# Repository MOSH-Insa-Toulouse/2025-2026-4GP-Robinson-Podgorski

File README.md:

##### 2025-2026 Podgorski Romain et Robinson Yanis
# **Projet de Capteur Graphite**

## Table des matières
- [Projet de Gapteur Graphite](#projet-de-capteur-graphite)
- [Contexte](#contexte)
- [Réalisation du projet](#réalisation-du-projet)
  - [1. Conception du capteur graphite](#1-conception-du-capteur-graphite)
    - [1.1 Matériel utilisé pour ce projet](#11-matériel-utilisé-pour-ce-projet)
    - [1.2 Principe de fonctionnement du capteur graphite](#12-principe-de-fonctionnement-du-capteur-graphite)
  - [2. Simulation electronique du circuit amplificateur avec LTSpice](#2-simulation-electronique-du-circuit-amplificateur-avec-ltspice)
    - [2.1 Principe de fonctionnement](#21-principe-de-fonctionnement)
    - [2.2 Simulations](#22-simulations)
  - [3. Conception de la PCB avec KiCad](#3-conception-de-la-pcb-avec-kicad)
    - [3.1 Réalisation des empreintes et de la schématique](#31-réalisation-des-empreintes-et-de-la-schématique)
    - [3.2 Placement et routage](#32-placement-et-routage)
    - [3.3 Visualisation 3D et vérifications](#33-visualisation-3d-et-vérifications)
  - [4. Réalisation du shield](#4-réalisation-du-shield)
    - [4.1 Impression de la PCB](#41-impression-de-la-pcb)
    - [4.2 Montage et soudure](#42-montage-et-soudure)
  - [5. Ecriture du code Arduino](#5-ecriture-du-code-arduino)
  - [6. Développement de l'application android couplée au code arduino avec MIT App Inventor](#6-développement-de-lapplication-android-couplée-au-code-arduino-avec-mit-app-inventor)
  - [7. Banc de test](#7-banc-de-test)
  - [8. Datasheet](#8-Datasheet)
- [Conclusion](#conclusion)
- [Références](#références)
- [Contacts](#contacts)
  - [Étudiants](#étudiants)
  - [Enseignants](#enseignants)

---

# Contexte

Dans un monde où la complexification de conception, de fabrication, d'utilisation et de réparation des dispositifs electroniques et appareils entraînent certaines dérives environnementales et de surconsommation, le développement de la low-tech est enjeu majeur de ces prochaines années.  

Dans ce contexte et dans le cadre de notre formation au Génie Physique de l'INSA Toulouse, nous avons développé au cours de ce projet un capteur de flexion simple de conception, de réalisation et de réparation, basé sur du graphite de crayon à papier. Nous l'avons intégré au sein d'un circuit électronique interactif couplé à un microcontrôleur Arduino, pilotable grâce à un code arduino et une application Android.

Le but final de ce capteur est de pouvoir le comparer avec un capteur de flexion industriel, et pouvoir répondre à la question :
*Ce capteur peut-il remplacer un capteur flex industriel ?*

Ce projet a été effectué en différentes étapes documentées dans ce README.

# Livrables

Ce projet contient 4 différents livrables :  
* Un shield Arduino pour le circuit électronique de nos composants
* Un code Arduino qui gère les différents composants ainsi que le banc de test
* Une application android APK qui gère l'interface avec le Arduino
* Une dtasheet du capteur de flexion

---

# Réalisation du projet

## 1. Conception du capteur graphite

### 1.1 Matériel utilisé pour ce projet
Pour réaliser ce projet, nous avons utilisé les composants électroniques suivant :
* 1 capteur en graphite fabriqué avec la mine d'un crayon à papier
* 1 carte Arduino UNO Rev 3
* 1 module Bluetooth HC-05
* 1 écran OLED SSD 1306
* 1 encodeur rotatif Keyes KY-040
* 1 capteur de flexion commercial LLC 1070
* 1 potentiomètre numérique MCP41100
* 2 supports IC pour le potentiomètre et l'amplificateur

Pour la réalisation du circuit amplificateur transimpédance, nous avons utilisé :
* 1 amplificateur opérationnel LTC1050
* 2 résistance 1kΩ
* 1 résistance 10kΩ
* 2 résistances 100kΩ
* 2 condensateurs 100nF
* 1 condensateur 1µF

### 1.2 Principe de fonctionnement du capteur graphite

Les mines de crayon sont composées de fines particules de graphite liées entre elles par des liants argileux. Le capteur de flexion en graphite repose sur le dépôt de ces particules sur un papier. En effet, les traces de crayon peuvent être considérées comme des films minces conducteurs constitués d'un réseau granulaire désordonné de particules de graphite percolées sur le papier. Les mines de crayon plus dures contiennent une proportion plus élevée de liants argileux tandis que les mines plus tendres contiennent une proportion plus élevée de particules de graphite résultant à une résistance moins élevée.

Face à une déformation mécanique, le réseau de ces particules est affecté, et la conduction électrique, qui s'effectue par le biais des contacts entre les particules voisines(effet tunnel), est donc fortement modifiée, augmentant ou diminuant la résistance du capteur :
* Sous contraction, la distance entre les particules diminue, favorisant les contacts entre paritucles et diminuant la résistance.
* Sous extension, la distance entre les particules augmente, rendant les contacts entre particules compliqués et augmentant donc la résistance.

C'est ainsi que nous pouvons mesurer la variation de flexion grâce à la variation de résistance au sein du capteur.

---

## 2. Simulation electronique du circuit amplificateur avec LTSpice

### 2.1 Principe de fonctionnement

La première étape de ce projet consiste à simuler le circuit amplificateur grâce au logiciel LTSpice.

Le capteur en graphite possède une résistance variable de l'ordre du GΩ. Si l'on applique la tension de 5V fournie par notre carte Arduino, le courant généré sera très faible, de l'ordre de la dizaine de nA. IL est donc nécessaire d'utiliser un circuit amplificateur pour pouvoir traiter ce signal.

Pour cela, nous utilisons un montage amplificateur transimpédance, qui permet de convertir le courant faible reçu par le capteur en une tension suffisante pour le convertisseur analogique-numérique (ADC) d'une carte Arduino. Le schéma du montage transimpédance est comme suit :

La résistance de shunt R1 permet la conversion de courant à tension, afin d'accepter un courant entrant venant du capteur. Ce montage est amplificateur à fort gain, non-inverseur et a l'avantage de pouvoir fonctionner avec seulement une alimentation positive. Cependant, la chute de tension sur R1 perturbe un peu la tension appliquée au capteur.

Des contraintes sont néanmoins présente pour le choix de l'amplificateur opérationnel. En effet, il doit accepter un faible courant d'entrée et une ultra-faible offset de tension afin de ne pas fausser les valeurs de tension transmises à l'ADC. L'amplificateur LTC1050 répond à ces critères.

Pour compléter ce montage, il est nécessaire de rajouter des filtres. En effet, le montage est très sensible, et vulnérable au bruit 50 Hz, aux horloges de circuits digitaux (microcontrôleur, afficheur, etc...) et aux transceivers RF (bluetooth, etc...). Une bande passante de 1 Hz est largement suffisante pour extraire toute l'information utile du capteur. Un filtrage anti-repliement est aussi indispensable en raison de l'échantillonage effectué par l'ADC, et pour cela il est donc nécessaire de faire fonctionner l'ADC à la plus grande fréquence sans perte de qualité, qui est de 15.4 kHz pour pour l'Arduino UNO. Le montage final est donc comme suivant :

Dans ce montage, plusieurs filtres sont en action :
* un filtre passif avec R1 et C1, avec $f_{c}= 16$ Hz, pour éviter que les bruits en courant de haute fréquence ne causent de la distorsion dans l'étage d'entrée
* un filtre actif avec R3 et C4, avec $f_{c}= 1,6$ Hz,pour un maximum d'efficacité sur l'amplificateur opérationnel
* un filtre passif avec C2 et R6, avec $f_{c}= 1,6$ Hz, pour retirer le bruit introduit en cours de traitement

De plus, la résistance en R5 protège l'amplificateur opérationnel contre les décharges électrostatiques, et forme avec C1 un filtre pour les bruits en tension.

Pour ce projet, nous avons aussi décidé de faire varier la résistance R2 avec un potentiomètre digital cablé en résistance variable, pour pouvoir adapter le gain en fonction du courant entrant. En effet, le gain de ce montage, exprimé comme ci-dessous, est inversement proportionnel à R2 :

$V_{ADC}=(1+\frac{R_{3}}{R_{2}})\frac{R_{1}}{R_{1}+R_{c}+R_{5}}V_{cc}$

Et nous pouvons donc remonter à la valeur de la résistance du capteur graphite :

$R_{c}=(1+\frac{R_{3}}{R_{2}})R_{1}\frac{V_{cc}}{V_{ADC}}-R_{1}-R_{5}$

### 2.2 Simulations

Afin de vérifier l'efficience de notre circuit amplificateur, nous l'avons simulé sur le logiciel LTSpice. Voici le résultat obtenu :

Le signal est bien amplifié de 500 mV à 1,00 V et peut donc être interprété par l'ARDUINO.

Nous avons également simulé un signal alternatif pour vérifier l'efficience des filtres présents sur notre circuit. Le résultat obtenu est le suivant :

On observe trois filtrages successifs du signal initial, correspondants au trois filtres de notre système. De plus, le signal est atténué d'environ 70dB à 50 Hz, comme souhaité. 

Ainsi, notre simulation est réussi.

---

## 3. Conception de la PCB avec KiCad

Une fois que nous avons validé la simulation sur LTSpice, nous sommes passés à la réalisation du shield Arduino : le circuit imprimé (PCB). Il comportera tous les composants cités dans la section [1.1 Matériel utilisé pour ce projet](#11-matériel-utilisé-pour-ce-projet), pour la réalisation du montage amplificateur ainsi que les différents composants additionnels (module bluetooth, écran OLED...).    Pour ce faire, nous utilisons la suite logicielle KiCad 9.0. Nous sommes passés par plusieurs étapes décrites dans la section suivante.

### 3.1 Réalisation des empreintes et de la schématique

Tout d'abord, nous avons créé les symboles de schématique non présents dans les librairies fournies par KiCad, nous les avons associé à des empreintes et un module 3D. Nous avons ensuite réalisé le schéma électrique comme suivant :

Certaines contraintes sur le choix des pins nous étaient imposées :
- Potentiomètre digital : pin SDI => pin D11 de l'Arduino, et pin SCK => pin D13 de l'Arduino
- Ecran OLED : pin SDA => pin A4 de l'Arduino, et pin SCK => pin A5 de l'Arduino
- Encodeur rotatoire : pin CLK => pin D2 de l'Arduino

Pour le restes des pins, nous étions libres de choisir les pins digitales ou analogiques de notre choix.

### 3.2 Placement et routage

La prochaine étape a été de placer l'organisation de la disposition des composants sur la PCB. Cette étape est cruciale car il faut pouvoir placer les composants startégiquement afin que les "routes" soient ordonnées et ne se surpassent pas, et qu'on utilise le moins de via possible. Le routage des différents composants a ensuite été effectué, et un plan de masse a été intégré pour stabiliser les potentiels et réduire le nombre de "routes". Voici la représentation de notre PCB :

### 3.3 Visualisation 3D et vérifications

Pour terminer, il a fallu vérifier la conformité du routage et des vias grâce à l'outil de contrôle des règles de conception, ainsi que visulaiser la PCB en 3D pour vérifier que les composants ne se chevauchent pas et améliorer l'ergonomie de la PCB (accès facile aux différents composants).

Une fois ces contrôles validées, la PCB est prête à être imprimée.

---

## 4. Réalisation du shield

### 4.1 Impression de la PCB

Une fois la PCB validée, nous avons pu passer à l'impression, par une méthode chimie (photolithographie). La fabrcation s'est faite en plusieurs étapes, avec l'aide de Cathy Crouzet (un grand merci à elle !) :
1. Vérification de la PCB avec KiCad (diamètre des trous, plan de masse...)
2. Impresssion du masque de gravure de la PCB
3. Insolation UV d'une plaquette d'epoxy recouverte d'une couche de cuivre et d'une couche de résine photosensible
4. Immersion de la plaquette dans un révélateur pour éliminer la résine non exposée (résine positive)
5. Immersion de la plaquette dans du perchlorure de fer pour graver les pistes 
6. Nettoyage de la plaquette avec de l'acétone pour éliminer la résine restante.

### 4.2 Montage et soudure

Une fois la PCB imprimée, nous avons pu percer les trous de notre plaquette et souder les différents composants. 
Lors des premiers tests du shield, nous nous sommes rendu compte de la présence de courts-circuits sur la plaquette, dûs à un problème lors de la fabrication. Nous avons donc gratté avec un cuteur pour supprimer ces connexions indésirables.
Un autre problème est survenu lors des tests. Nous nous sommes rendus compte que nou avions relié les pins TX et RX du modules bluetooth aux pins 0 et 1 de l'Arduino, réservées à la communication par port série. Nous avons donc coupé ces routes et rajouté des fils pour les relier aux pins 7 et 8 qui etaient libres (à nouveau un grand merci, à Jérémie Grisolia pour nous avoir aidé à régler ces problèmes)

Une fois ces problèmes résolus, le shield Arduino a parfaitement fonctionné.

---

## 5. Ecriture du code Arduino

Le code Arduino comprend plusieurs fonctions contrôlant les différents modules de notre PCB. Les différents modules sont au préalable calibrés sur les bons pins.

**Configuration de chaque module**

On associe des pins à chaque module en en-tête du code pour la communication.

**Le setup (setup())**

Cette fonction à l'exécution du code :
* ouvre le canal de transmission avec le module Bluetooth avec un Baud rate de 9600.
* met le potentiomètre digital en veille
* Déclare les canaux de la clock, des datas et du switch de l'encodeur rotatoire comme des canaux d'entrée et active les pull-ups de canaux de la clock et des datas pour garantir la fiabilité des valeurs
* active le protocole SPI pour lire rapidement les données et règle l'horloge
* déclenche l'interruption matérielle en cas de front montant pour lire la valeur de la position de l'encodeur rotatoire
* Initialise l'écran OLED

**Le réglage du potentiomètre (setPotWiper(int addr, int pos))**

Cette fonction règle la valeur du potentiomètre en fonction de la position et calcule la résistance associée et l'affiche de le moniteur Serial.

**La mesure de le résistance du capteur graphite (graphiteMeas())**

On mesure une valeur de tension numérique aux bornes du capteur graphite entre 0 et 1023. On la convertit en tension analogique entre 0 et 5V et on calcule la résistance à partir de cette tension.

**La mesure de la résistance du flex sensor (flexMeas())**

Le principe de calcul est le même que celui utilisé pour le capteur graphite mais appliqué dans ce cas au flex sensor. 

**L'appui sur le bouton (get_encodButton())**

Cette fonction détecte lorsque le bouton de l'encodeur rotatoire est pressé et filtre les faux-déclenchements (anti-rebonds)

**La rotation de l'encodeur rotatoire (get_encodPos())**

Cette fonction détecte le sens de rotation de l'encodeur rotatoire et met à jour sa position.

**La calibration du potentiomètre numérique (calibration())**

Cette fonction calibre la valeur du potentiomètre numérique pour déterminer une valeur de tension aux bornes du capteur en graphite soit de 2,5 V (la valeur médiane). La valeur du potentiomètre est également transférée à l'application via le module Bluetooth.

**La construction de l'écran OLED (set_OLED_screen(byte tailleDeCaractere) et OLED_InverseColor(bool Inverse))**

Ces fonctions initialisent l'écran OLED aux dimensions souhaitées et écrivent les textes en noir sur fond blanc, respectivement.

**L'utilisation de l'écran OLED (OLED_manage_menu())**

Cette fonction affiche le menu selon la position de l'encodeur (Calibration, Meas on ou Meas off) et exécute l'action lorsqu'on appuise sur le bouton. Les données sont également envoyées à l'application.

**La fonction de rafraichissement (loop())**

Cette fonction lit la position de l'encodeur pour connaître la position du curseur sur le menu OLED, le gère, fait des mesures de réssitances du capteur graphite et du flex sensor si le curseur est sur l'onglet "Meas on" et envoue ces données à l'application via la Bluetooth.

## 6. Développement de l'application android couplée au code arduino avec MIT App Inventor

L'application s'articule en 5 points différents :

* L'ouverture du canal entre l'Arduino et l'appli via la connexion Bluetooth
* La récupération des données brutes
* Le tri des données en fonction du chiffre reçu (1 pour le calibrage, 2 pour la réception et l'affichage des mesures de résistance, 3 pour l'arrêt de la transmission et de l'affichage des mesures de résistance)
* L'afffichage des données sur la face avant, dans des spins box pour le calibrage et les valeurs de résistance en direct du capteur graphite et du flex sensor et sur des graphes des valeurs de résistance du capteur graphite et du flex sensor en fonction du temps
* La fermeture du canal

L'utilisateur peut intéragir avec l'appli grâce à la face avant. La connexion entre l'Arduino et l'appli est notamment établie lorsque l'utilisateur clique sur le bouton "Connexion ARDUINO Bluetooth".

## 7. Banc de test

Nous avons utilisé un banc de test pour caractériser notre capteur graphite. Ce banc de test est un cylindre qui possède différentes valeurs de rayon de 1 à 2,5 cm. Nous avons dès lors calculé la variation de résistance $\frac{\Delta R}{R_0}$ en fonction de la déformation $\epsilon = \frac{e}{D}$, pour une épaisseur de papier e = 0,02 cm.

Nous obtenons des courbes de caractérisations pour une déformation en tension et en compression avec différents types de crayons à papier.

Dans le cas d'une déformation en tension, plus la déformation est grande, plus la variation relative est grande. L'inverse se produit en compression. Cela s'explique par le fait que les atomes s'éloignent en tension ce qui augmente la résistance, à l'inverse de la compression.

En outre, plus le crayon est gras, plus la variation relative est faible en tension (HB, 2B, 4B) ; les crayons gras contiennent plus d'atomes de carbone.

Les résultats obtenus dépendent fortement de la quantité de crayon déposé sur le papier. Ainsi, les résultats obtenus ne sont pas reproductibles.

---

# Datasheet

Nous avons réalisé une datasheet du capteur graphite. Elle est disponible sur notre github.

---

# Conclusion

La création d'un capteur de la première étape à l'étape de fin a été d'un grand enrichissement.
Nous avons eu l'occasion de toucher à divers outils pour la création de notre capteur (LTSPice, KiCad, Arduino, MIT App Inventor). En somme, ce projet est un avant-goût du travail actuel d'un ingénieur.

En outre, notre capteur est fonctionnel et simple d'utilisation. Les valeurs obtenues sont cohérentes,  et nous avons pu remplir l'ensemble du cahier des charges.

De plus, les capteurs graphites fabriqués ont une meilleure sensibilité que celle des capteurs industriellles flex sensor. Néanmoins, leur durée de vie est très faible devant celle du flex sensor. Ainsi, les capteurs graphites ne sont pas industrialisables.

---

# Contacts

## Étudiants
- **Romain Podgorski** : podgorski@insa-toulouse.fr  
- **Yanis Robinson** : robinson@insa-toulouse.fr  

## Enseignants
- **Jérémie Grisolia** : jeremie.grisolia@insa-toulouse.fr
- **Benjamin Mestre** : benjamin.mestre@scalian.com  
- **Arnauld Biganzoli** : arnauld.biganzoli@insa-toulouse.fr  
- **Cathy Crouzet** : crouzet@insa-toulouse.fr

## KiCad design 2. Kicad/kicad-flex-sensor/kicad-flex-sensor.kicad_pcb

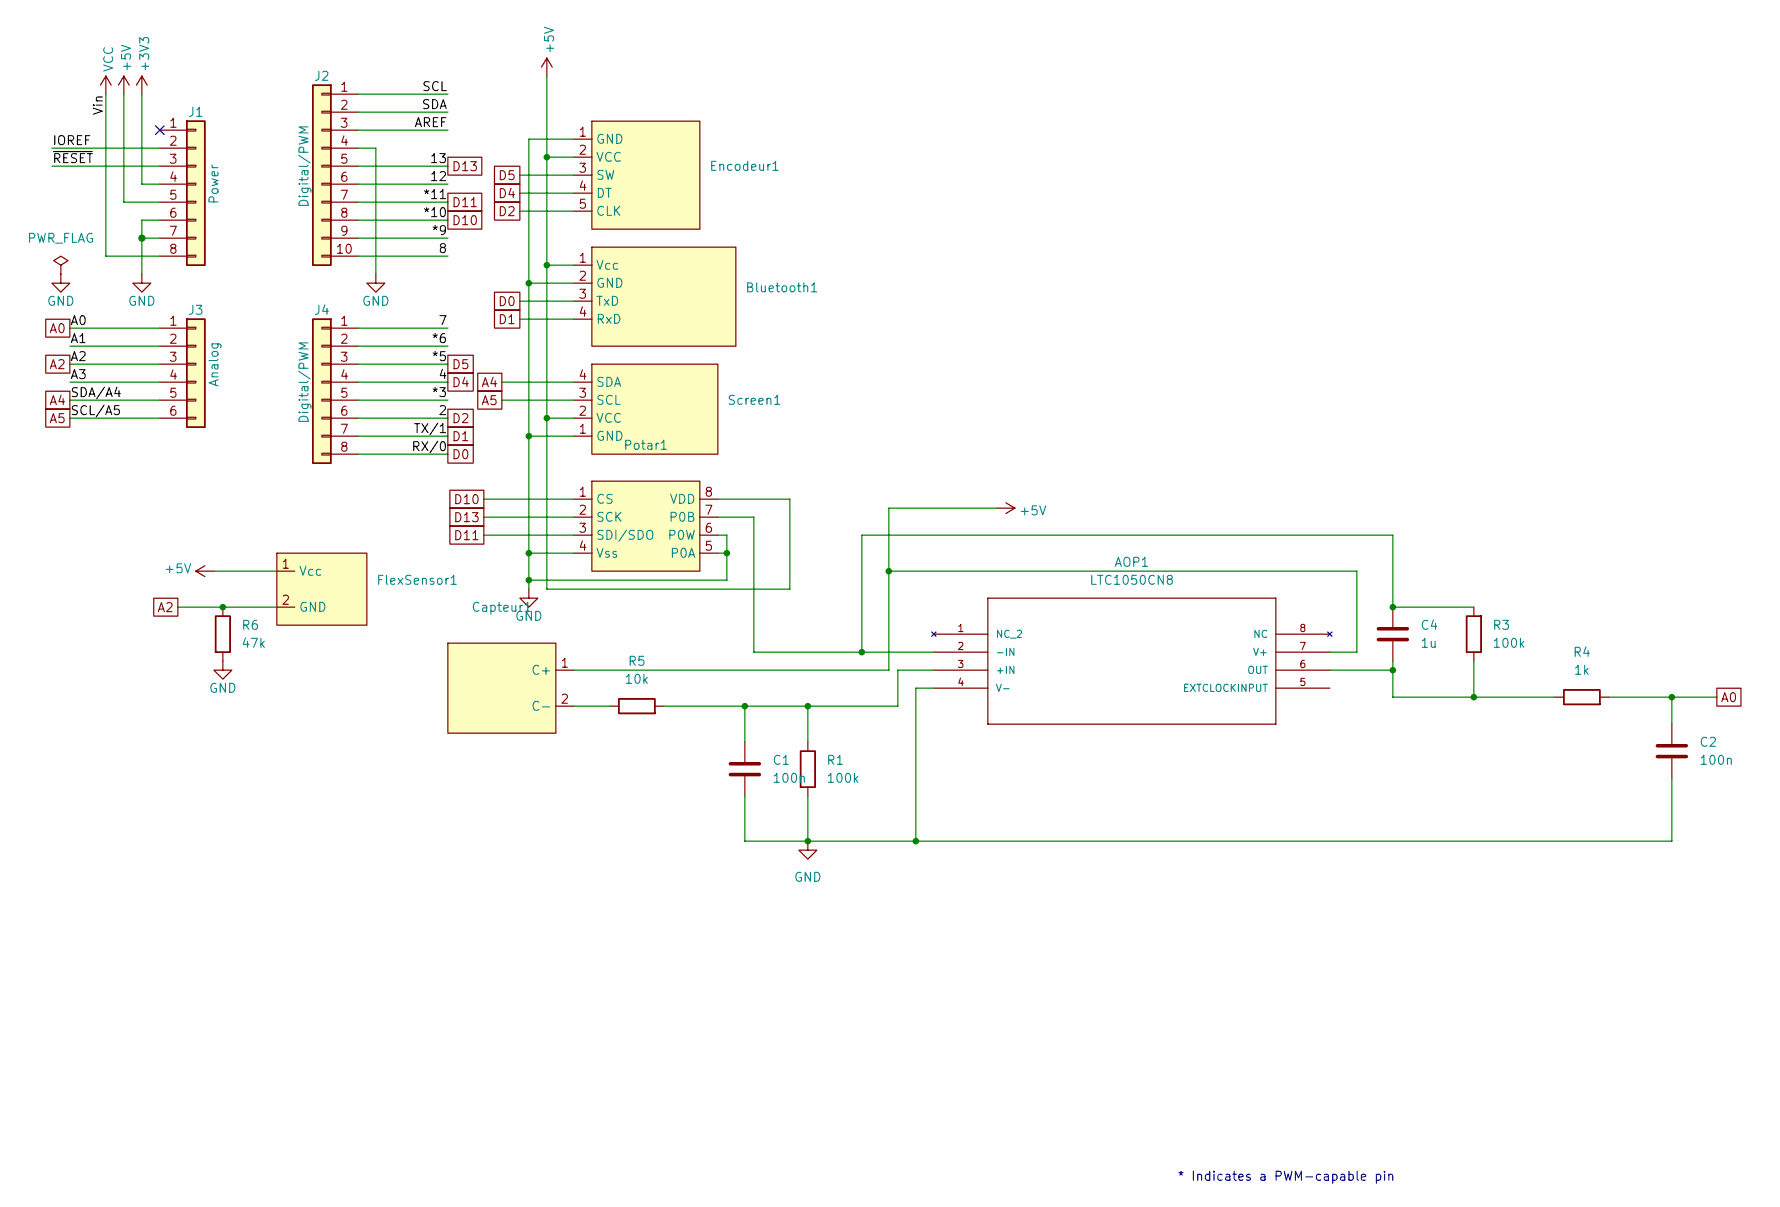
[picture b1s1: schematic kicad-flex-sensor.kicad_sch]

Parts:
AOP1: LTC1050CN8; PDIP-8_N; MANUFACTURER_PART_NUMBER ltc1050cn8
Bluetooth1: Bluetooth_empreinte
C1, C2: 100n; C_Disc_D4.7mm_W2.5mm_P5.00mm
C4: 1u; C_Rect_L7.0mm_W4.5mm_P5.00mm
Capteur1: Capteur
Encodeur1: Encodeur_rotatoire
FlexSensor1: Capteur
J1: Power; PinSocket_1x08_P2.54mm_Vertical
J2: Digital/PWM; PinSocket_1x10_P2.54mm_Vertical
J3: Analog; PinSocket_1x06_P2.54mm_Vertical
J4: Digital/PWM; PinSocket_1x08_P2.54mm_Vertical
Potar1: DIP-8_W7.62mm_LongPads
R1, R3: 100k; R_Axial_DIN0207_L6.3mm_D2.5mm_P7.62mm_Horizontal
R4: 1k; R_Axial_DIN0207_L6.3mm_D2.5mm_P7.62mm_Horizontal
R5: 10k; R_Axial_DIN0207_L6.3mm_D2.5mm_P7.62mm_Horizontal
R6: 47k; R_Axial_DIN0207_L6.3mm_D2.5mm_P7.62mm_Horizontal
Screen1: OLED

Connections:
+3V3: J1.4
+5V: AOP1.7 (V+), Bluetooth1.1 (Vcc), Capteur1.1 (C+), Encodeur1.2 (VCC), FlexSensor1.1 (Vcc), J1.5, Potar1.8 (VDD), Screen1.2 (VCC)
/7: J4.1
/8: J2.10
/12: J2.6
/*3: J4.5
/*6: J4.2
/*9: J2.9
/A1: J3.2
/A3: J3.4
/AREF: J2.3
/IOREF: J1.2
/SCL: J2.1
/SDA: J2.2
/~RESET: J1.3
A0: C2.1, J3.1, R4.2
A2: FlexSensor1.2 (GND), J3.3, R6.1
A4: J3.5, Screen1.4 (SDA)
A5: J3.6, Screen1.3 (SCL)
D0: Bluetooth1.3 (TxD), J4.8
D1: Bluetooth1.4 (RxD), J4.7
D2: Encodeur1.5 (CLK), J4.6
D4: Encodeur1.4 (DT), J4.4
D5: Encodeur1.3 (SW), J4.3
D10: J2.8, Potar1.1 (CS)
D11: J2.7, Potar1.3 (SDI/SDO)
D13: J2.5, Potar1.2 (SCK)
GND: AOP1.4 (V-), Bluetooth1.2 (GND), C1.2, C2.2, Encodeur1.1 (GND), J1.6, J1.7, J2.4, Potar1.4 (Vss), Potar1.5 (P0A), Potar1.6 (P0W), R1.2, R6.2, Screen1.1 (GND)
unnamed: AOP1.3 (+IN), C1.1, R1.1, R5.2
unnamed: AOP1.2 (-IN), C4.1, Potar1.7 (P0B), R3.2
unnamed: AOP1.6 (OUT), C4.2, R3.1, R4.1
unnamed: Capteur1.2 (C-), R5.1
VCC: J1.8

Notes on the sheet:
* Indicates a PWM-capable pin

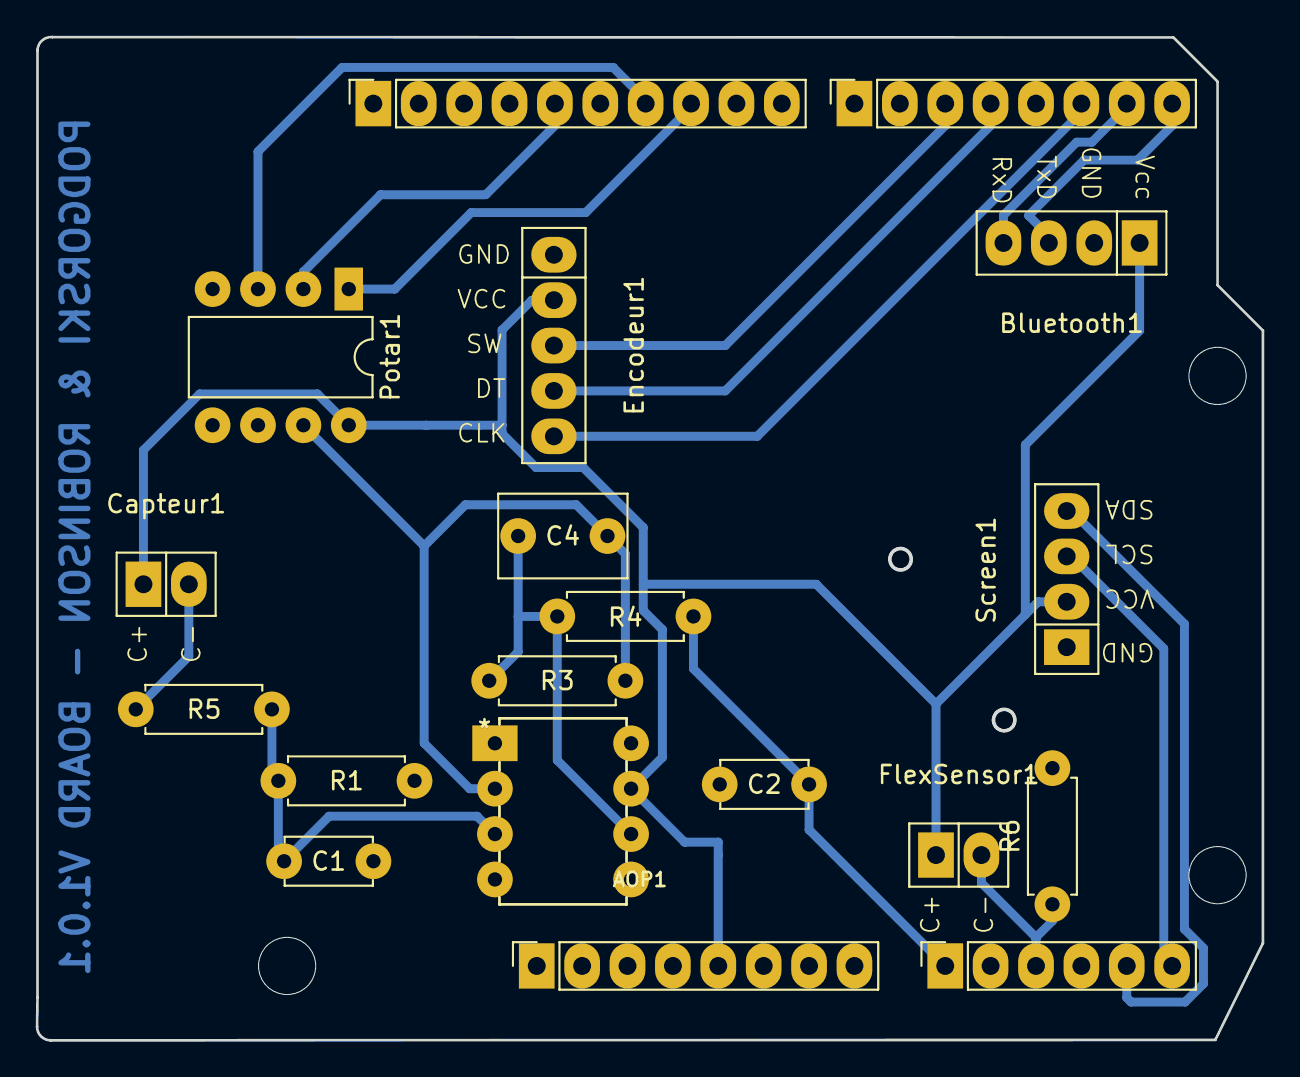
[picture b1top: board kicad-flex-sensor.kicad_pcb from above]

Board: 2 copper layers, 68.6 x 56.1 mm, 22 parts (0 on the bottom side), 18 nets.

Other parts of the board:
MH2, MH3, MH4: MountingHole_3.2mm

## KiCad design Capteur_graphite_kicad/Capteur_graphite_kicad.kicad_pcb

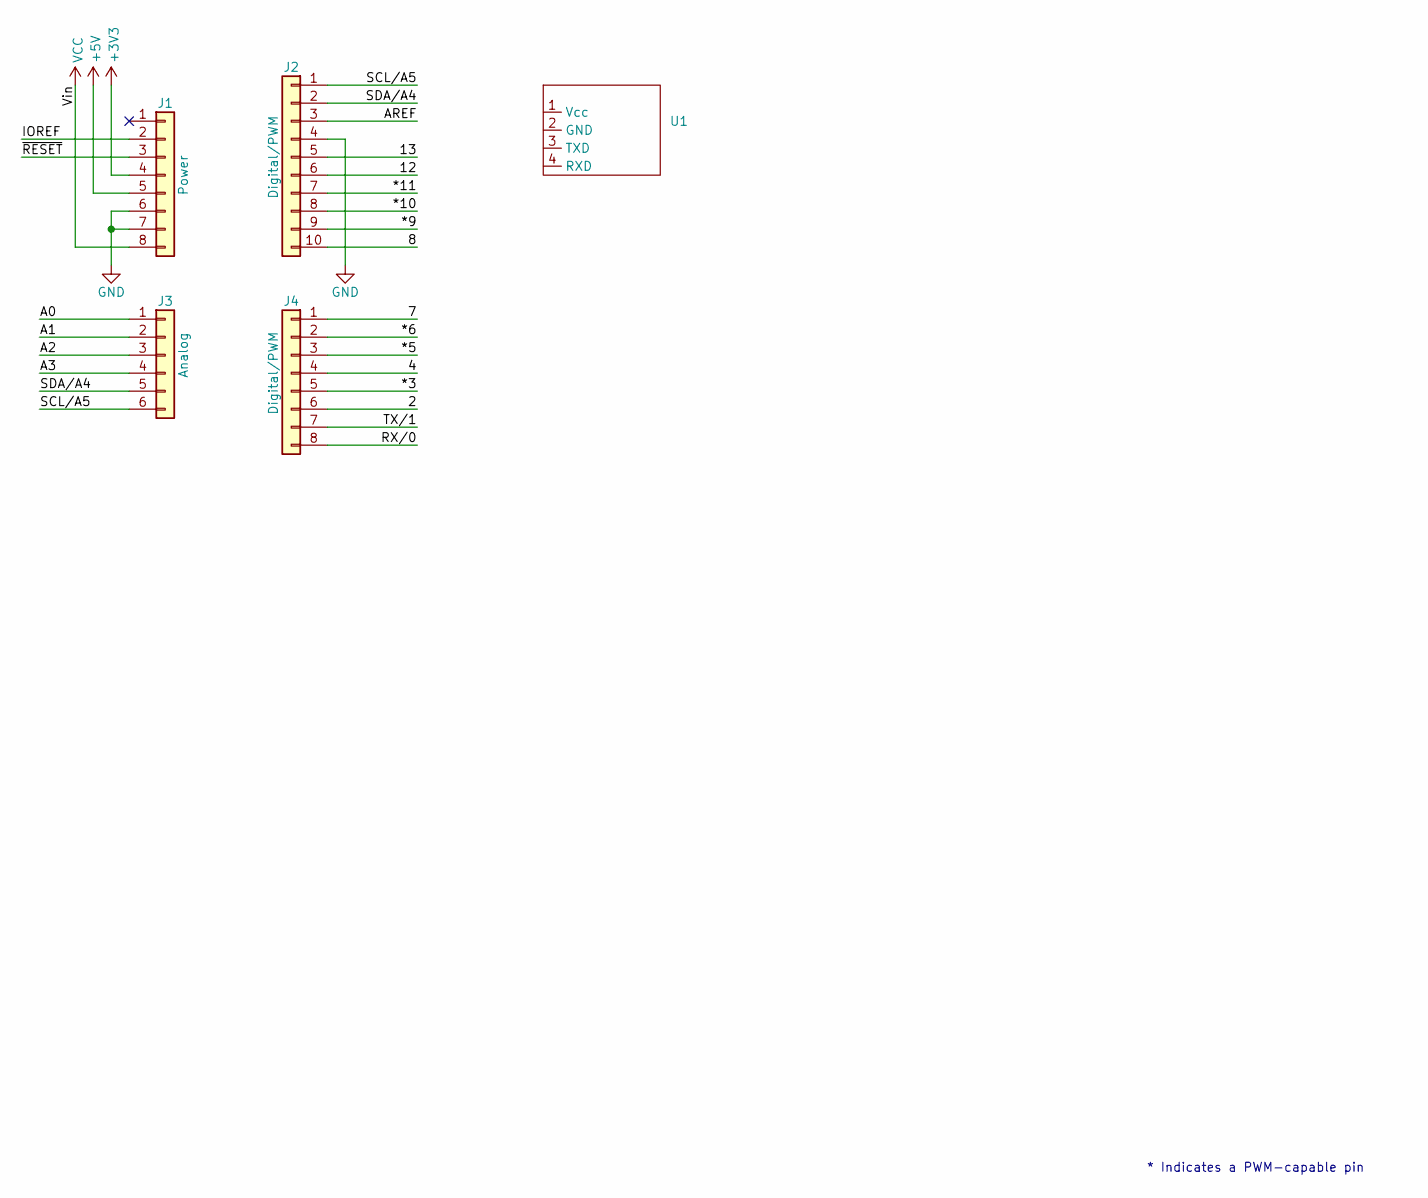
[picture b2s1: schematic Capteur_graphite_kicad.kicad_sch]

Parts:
J1: Power; PinSocket_1x08_P2.54mm_Vertical
J2: Digital/PWM; PinSocket_1x10_P2.54mm_Vertical
J3: Analog; PinSocket_1x06_P2.54mm_Vertical
J4: Digital/PWM; PinSocket_1x08_P2.54mm_Vertical
U1: Bluetooth2

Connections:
+3V3: J1.4
+5V: J1.5
/2: J4.6
/4: J4.4
/7: J4.1
/8: J2.10
/12: J2.6
/13: J2.5
/*3: J4.5
/*5: J4.3
/*6: J4.2
/*9: J2.9
/*10: J2.8
/*11: J2.7
/A0: J3.1
/A1: J3.2
/A2: J3.3
/A3: J3.4
/AREF: J2.3
/IOREF: J1.2
/RX/0: J4.8
/SCL/A5: J2.1, J3.6
/SDA/A4: J2.2, J3.5
/TX/1: J4.7
/~RESET: J1.3
GND: J1.6, J1.7, J2.4
VCC: J1.8

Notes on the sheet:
* Indicates a PWM-capable pin

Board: 2 copper layers, 9 parts (0 on the bottom side), 3 nets, no tracks yet.

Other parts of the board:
MH1, MH2, MH3, MH4: MountingHole_3.2mm

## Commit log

2026-02-10 Création du fichier KicAD
2026-02-10 Add REAME
2026-02-15 add bluetooth symbol and footprint
2026-02-15 suppr 3d models qui marchent pas
2026-02-15 rm res and cap
2026-02-17 Add des modèles 3D
2026-02-17 add schema OLED
2026-02-20 add plein de choses
2026-02-20 Routage
2026-02-20 Les trucs que j'avais pas sauvegardé
2026-02-26 routage qui marche !
2026-03-06 Finito !
2026-04-09 Organisation du github - kicad
2026-04-09 change place README.md
2026-04-09 Début README avec titres et tables des matières
2026-04-09 same
2026-04-09 README context
2026-04-09 README partie 1
2026-04-09 test readme
2026-04-09 fin test
2026-04-10 LTSpice
2026-04-10 Partie KiCad (manque la visu 3D)
2026-04-10 Ortograffe
2026-04-13 Réalisation shield et add fichiers LTSpice
2026-04-13 push
2026-04-13 Complément de plusieurs choses
2026-04-13 Création datasheet
2026-04-13 move datasheet
2026-04-14 Add arduino final
2026-04-16 Modif datasheet
2026-04-16 Modifs datasheet
2026-04-16 add sensi datasheet
2026-04-16 Add code arduino et test bench
2026-04-16 Mise en forme datasheet
2026-04-17 Modifs Kicad flex sensor
2026-05-28 Rédaction du la partie d'explication du code Arduino sur le Read.me
2026-05-28 Rédaction de de la partie application android du Read.me
2026-05-28 Ajout de la datasheet en PDF
2026-05-28 Ajout partie Arduino Read.me
2026-05-28 Ajout des screen de l'app et commentaires arduino
2026-05-28 fin comments arduino
2026-05-29 Ecriture conclusion ReadMe
2026-05-30 FInition github
2026-05-30 FInition Read Me
2026-05-30 FIn du Github

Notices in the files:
parts and their libraries:
COPYRIGHT: Copyright C 2016 Accelerated Designs. All rights reserved
